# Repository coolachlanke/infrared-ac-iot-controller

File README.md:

# Wireless Smart IoT IR Blaster for AC Unit

Wireless control of Daikin split system air conditioning unit using IR LED + ESP32-S3.

---
Take a look a the fully sick 3D render:

---
..and now take a look at the fully sick assembled board:

** Under construction **

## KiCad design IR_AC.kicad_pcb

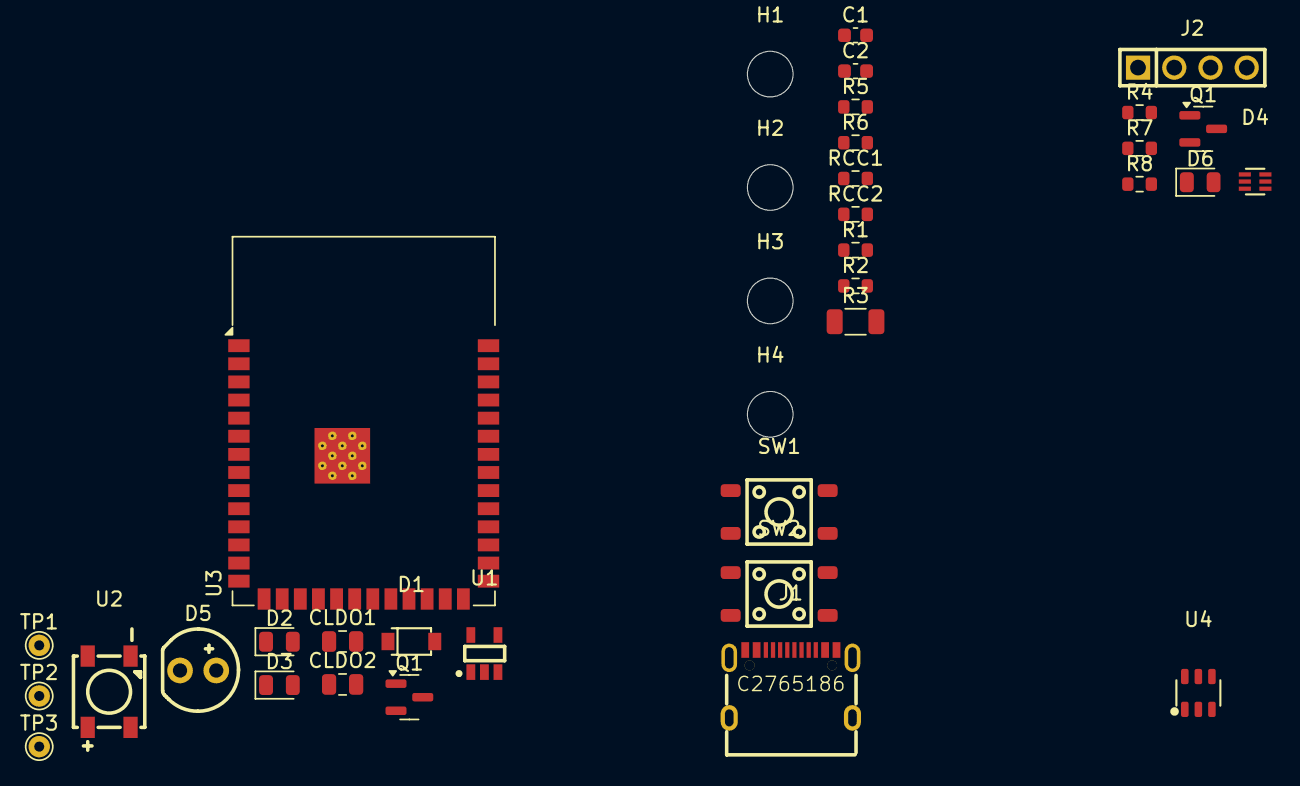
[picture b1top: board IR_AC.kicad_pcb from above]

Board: 2 copper layers, 37 parts (0 on the bottom side), 20 nets, no tracks yet.

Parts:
C1, C2: 1u; C_0603_1608Metric
CLDO1, CLDO2: 1u; C_0805_2012Metric
D1: 1N5819HW
D2, D3: GREEN; LED_0805_2012Metric
D4: PRTR5V0U2X; SOT-666-6_L1.6-W1.2-P0.50-LS1.6-BR
D5: LED; IR_LED_TH_5MM
D6: RED; LED_0805_2012Metric
H1, H2, H3, H4: MountingHole; MountingHole_3.2mm_M3
J1: TYPE-C 16PIN 2MD(073); USB-C-SMD_TYPE-C-6PIN-2MD-073
J2: Conn_01x04_Pin; HDR-TH_4P-P2.54-V-M
Q1: NPN; SOT-23
Q1#2: NMOS; SOT-23
R1: 680R; R_0603_1608Metric
R2: 2k2; R_0603_1608Metric
R3: 30R; R_1206_3216Metric
R4: 330R; R_0603_1608Metric
R5, R6: 10k; R_0603_1608Metric
R7: 100R; R_0603_1608Metric
R8: 100k; R_0603_1608Metric
RCC1, RCC2: 5.1k; R_0603_1608Metric
SW1, SW2: SW_Push; BTN_L45_W45
TP1, TP2, TP3: TestPoint; TestPoint_THTPad_D1.5mm_Drill0.7mm
U1: AP2112K-3.3TRG1; AP2112K-3.3
U2: WS2812B_5050
U3: ESP32-S3-WROOM-1
U4: USBLC6-4; SOT-23-6_L2.9-W1.6-P0.95-LS2.8-BL

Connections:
+3V3: CLDO2.1, R1.2, R5.2, R6.2, TP1.1, U1.5 (VOUT), U3.2 (3V3)
/CC1: J1.4 (CC1), RCC1.2, U4.5 (S4)
/CC2: J1.10 (CC2), RCC2.2, U4.1 (S1)
/V_BUS: D1.2 (A), J1.2 (VBUS), J1.11 (VBUS)
BOOT: C2.1, R6.1, SW2.2, U3.27 (IO0)
D+: D4.2 (D+), U3.14 (USB_D+)
D-: D4.1 (D-), U3.13 (USB_D-)
EN: C1.1, R5.1, SW1.2, U3.3 (EN)
GND: C1.2, C2.2, CLDO1.2, CLDO2.2, D2.1 (K), D3.1 (K), D4.3 (GND), J1.1 (GND), J1.12 (GND), J1.13 (SHELL), J1.14 (SHELL), Q1.3 (E), Q1#2.3 (S), R8.1, RCC1.1, RCC2.1, SW1.1, SW2.1, U1.2 (GND), U2.3 (GND), U3.1 (GND), U3.40 (GND), U3.41 (GND), U4.2 (GND)
IR_LED_DRIVE: Q1.2 (B), R7.2, U3.21 (IO13)
LED_STATUS: U2.4 (DIN), U3.20 (IO12)
unnamed: D2.2 (A), R1.1
unnamed: D3.2 (A), R2.1
unnamed: D5.2 (A), R3.1, TP3.1
unnamed: D5.1 (K), D6.1 (K), Q1#2.1 (D)
unnamed: D6.2 (A), R4.1
unnamed: J1.5 (DN2), J1.7 (DN1), U4.4 (S3)
unnamed: J1.6 (DP1), J1.8 (DP2), U4.3 (S2)
unnamed: Q1#2.2 (G), R7.1, R8.2
VDC: CLDO1.1, D1.1 (K), D4.4 (VCC), R2.2, R3.2, R4.2, TP2.1, U1.1 (VIN), U1.3 (EN), U2.1 (VDD)

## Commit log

2025-08-13 Erste Ubertragung
2025-09-03 late night work on led current
2025-09-06 Finished schematic
2025-09-07 Routing + DRC complete. Ordered with JLCPCB + LCSC
2025-09-07 Added render
2025-09-07 Added render2
2025-09-07 Added render324345
2025-09-07 Added render324345 again innit
